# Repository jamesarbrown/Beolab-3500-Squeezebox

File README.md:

# Beolab-3500-Squeezebox

This project is to convert and Bang and Olufsen Beolab 3500 into a Logitech Media Server / Slimdevices Squeezebox using Raspberry Pi and PiCorePlayer.

My first Squeezebox1 I bought from the US direct, long long before it was into the UK and since the range has been obsoleted by Logitech I wanted something a bit more than a streamer alone. There is a lot of B&O stuff in our family and it was a natural way to go, and most elegant equipment that has like all electronic stuff is soon out of date.

The project has a requirement for 3d printed parts and homemade PCBs

In no way is this project affiliated or representative of Bang and Olufsen, Logitech or Slimdevices. I have utilised the logos in my fascia designs, but if they need removing as companies sometimes do, I can do that, but don't feel this harms your brand identities.

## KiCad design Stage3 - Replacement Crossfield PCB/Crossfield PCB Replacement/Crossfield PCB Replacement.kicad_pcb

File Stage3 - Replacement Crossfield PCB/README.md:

## Stage 3 - Replacement Crossfield and Ribbon Cables

### Ribbon Cable Replacements

| Function            | New Length    | Ways | Socket on Beolab   | RS PN Plugs   |
| ------------------- |:-------------:| :---:| :----------------: | ------------: |
| Right Hand Side Amp | 380mm         | 8    | P2                 | 680-5148      |
| Left Hand Side Amp  | 520mm         | 8    | P2                 | 680-5148      |
| Right Hand Side Amp | 370mm         | 12   | P18                | 680-4933      |
| TX "Left"           | 520mm         | 4    | P21                | 341-7349      |

Note 10 way ribbon P17 to P5 is removed and not replaced. On ribbon cable bought a length of 14 way and cut down for other sections

In later stages the right hand side and left hand amps will be swapped around to create space for the crossfield PCB

## Crossfield PCB Folders

I made the PCB utilising laser printer thermal transfer method. 

In the following folders please finds

### PDFs

Crossfield PCB.pdf - The PCB to Print

Crossfield Schematic.pdf - The Schematic of the above PCB

### Crossfield PCB Replacement (KiCAD Project)
The original KiCAD Design files, including the TE connectivity plugs and so on

#### Notes 
I had difficulty in nailing down the PFAIL and PLIM functions, so copied the way they originally were immplemented into the B&O microcomputer. Then used a BC549 to separate the circuit from the Raspberry. My suspicion was I could pull down the 3v3 directly, but went for this way to achieve some security.

### 3d from Kicad of PCB

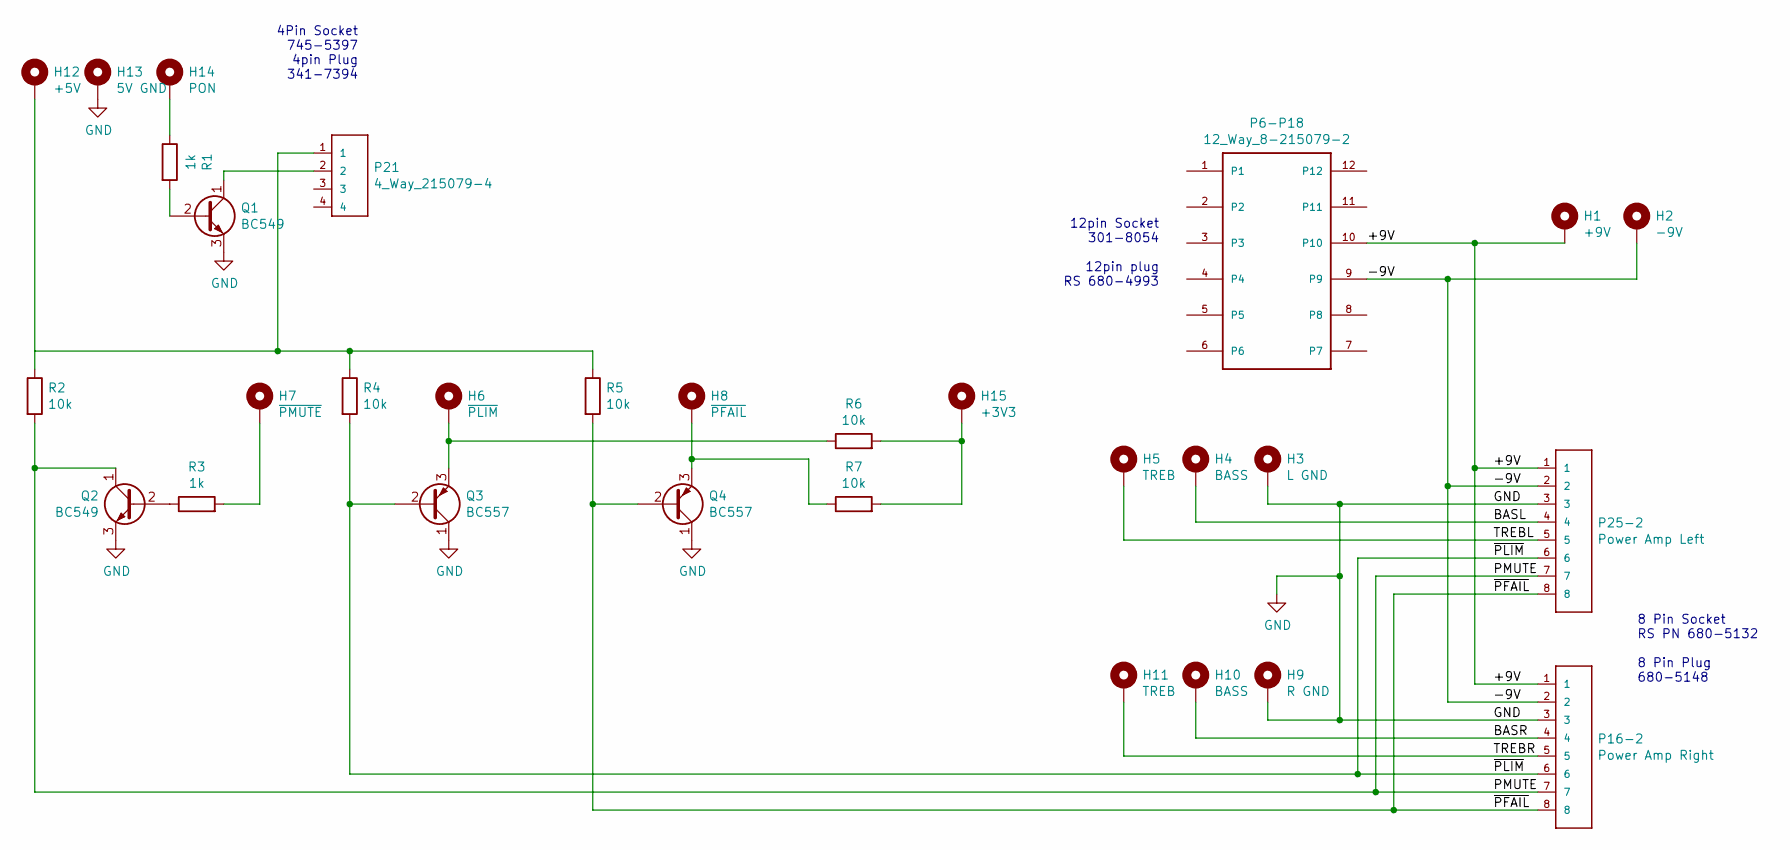
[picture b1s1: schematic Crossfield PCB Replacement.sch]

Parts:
H1: +9V; SolderWirePad_1x01_Drill1.2mm
H2: -9V; SolderWirePad_1x01_Drill1.2mm
H3: L GND; SolderWirePad_1x01_Drill1.2mm
H4, H10: BASS; SolderWirePad_1x01_Drill1.2mm
H5, H11: TREB; SolderWirePad_1x01_Drill1.2mm
H6: ~PLIM; SolderWirePad_1x01_Drill1.2mm
H7: ~PMUTE; SolderWirePad_1x01_Drill1.2mm
H8: ~PFAIL; SolderWirePad_1x01_Drill1.2mm
H9: R GND; SolderWirePad_1x01_Drill1.2mm
H12: +5V; SolderWirePad_1x01_Drill1.2mm
H13: 5V GND; SolderWirePad_1x01_Drill1.2mm
H14: PON; SolderWirePad_1x01_Drill1.2mm
H15: +3V3; SolderWirePad_1x01_Drill1.2mm
P6-P18: 12_Way_8-215079-2; TE_8-215079-2
P16-2: Power Amp Right; TE_215079-8
P21: 4_Way_215079-4; TE_215079-4
P25-2: Power Amp Left; TE_215079-8
Q1, Q2: BC549; TO-92_Inline
Q3, Q4: BC557; TO-92_Inline
R1, R3: 1k; R_Axial_DIN0204_L3.6mm_D1.6mm_P7.62mm_Horizontal
R2, R4, R5, R6, R7: 10k; R_Axial_DIN0204_L3.6mm_D1.6mm_P7.62mm_Horizontal

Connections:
/+9V: H1.1, P6-P18.10, P16-2.1, P25-2.1
/-9V: H2.1, P6-P18.9, P16-2.2, P25-2.2
/BASL: H4.1, P25-2.4
/BASR: H10.1, P16-2.4
/PMUTE: P16-2.7, P25-2.7, Q2.1 (C), R2.2
/TREBL: H5.1, P25-2.5
/TREBR: H11.1, P16-2.5
/~PFAIL: P16-2.8, P25-2.8, Q4.2 (B), R5.2
/~PLIM: P16-2.6, P25-2.6, Q3.2 (B), R4.2
GND: H3.1, H9.1, H13.1, P16-2.3, P25-2.3, Q1.3 (E), Q2.3 (E), Q3.1 (C), Q4.1 (C)
unnamed: H6.1, Q3.3 (E), R6.1
unnamed: H7.1, R3.2
unnamed: H8.1, Q4.3 (E), R7.1
unnamed: H12.1, P21.1, R2.1, R4.1, R5.1
unnamed: H14.1, R1.1
unnamed: H15.1, R6.2, R7.2
unnamed: P21.2, Q1.1 (C)
unnamed: Q1.2 (B), R1.2
unnamed: Q2.2 (B), R3.1

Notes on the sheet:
8 Pin Socket RS PN 680-5132 8 Pin Plug 680-5148
12pin Socket 301-8054 12pin plug RS 680-4993
4Pin Socket 745-5397 4pin Plug 341-7394

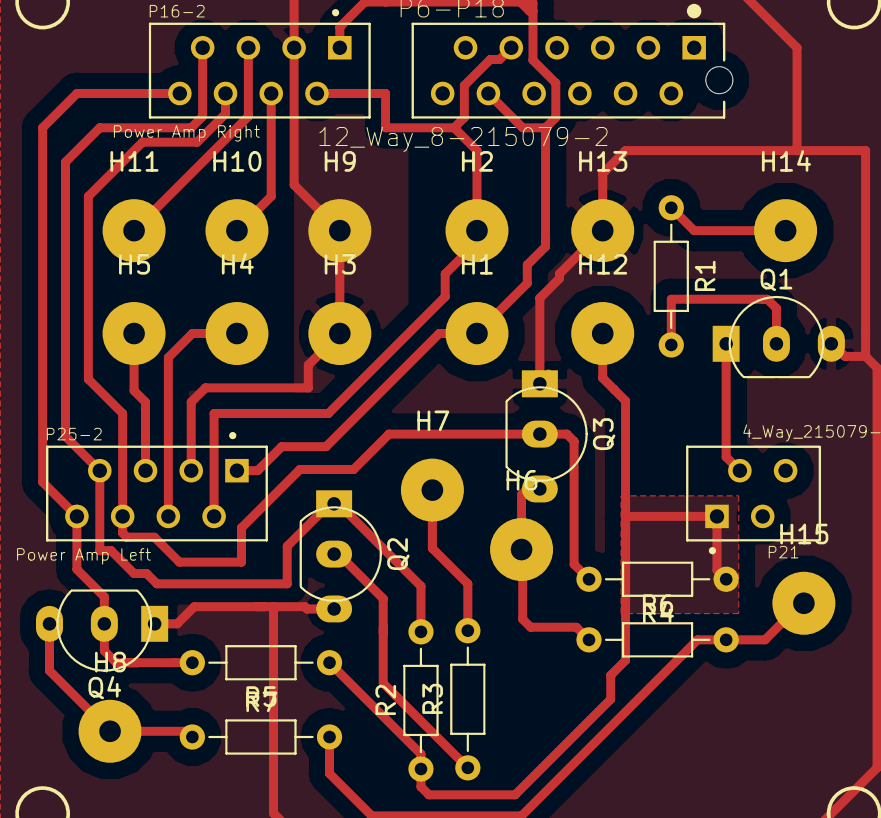
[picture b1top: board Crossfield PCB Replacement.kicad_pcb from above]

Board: 2 copper layers, 30 parts (0 on the bottom side), 19 nets.

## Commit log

2019-03-10 Added Support Info
2019-03-10 Added replacement speaker info
2019-03-10 Images new speaker
2019-03-10 Moved Image to image folder
2019-03-10 Rename of Image
2019-03-10 Added flashforge printer files
2019-03-10 Added Solidworks Part and Assy files
2019-03-10 Added Images of Fascia
2019-03-10 Added STL
2019-03-11 Added PCB and Schematic
2019-03-11 Added KiCAD FIles
2019-03-17 Fixed mains cable position holes
2019-03-17 Flashforge printer files
2019-03-17 First Stage of PSU Conversion
2019-03-17 Renamed Folders
2019-03-17 Added Flashforge printer files for speaker bracket
2019-03-17 Renamed Folder and rescalled image
2019-03-17 Modifications to Left TC assy
2019-03-17 Adjusted Cable holes to suit RS PN 817-8873
2019-03-17 Added Images in build Rear Casing
2019-03-17 New Printer Files for Rear Casing
2019-03-17 Fixed Pin No Ordering on 12 Way Connector
2019-03-18 Changed PCB now has USB PSU
    The B&O PSU failed to provide enough mA for the raspberry. Now the switchmode PSU has been removed and replaced with a standard USB brick.
2019-03-18 Amended the Ribbon Cables
    Removed the switchmode PSU at this stage
2019-03-18 Updated Crossfield Designs
    Removed the 14 way connector to the Switchmode PSU and added a 4 way connector direct to Left TX (operating the main power relay)
2019-03-18 Added 3dimage of Crossfield
2019-03-18 Added 3d Image
2019-03-18 Added rear plastics README
2019-03-19 Added images of USB power plug Stage
2019-03-23 Fixed Pinout on 12 pin connector
2019-03-23 Fixed PCB to suit new pin out
2019-03-23 PCB tweaks
2019-03-31 Updated PCB following tests on PMUTE
2019-03-31 Removed Duplicate PDFs
2019-03-31 Corrected PCB Image
2019-03-31 Widened legs on Transistors for easier working
2019-03-31 Fixed broken track
2019-04-06 Loaded correct schematic image
2019-04-06 Corrected to reflect the 3rd PSU attempt
2019-04-06 Added Overview Wiring
2019-04-06 Updated Readme to include wiring diagram
2019-04-06 Auto Power Script
2019-04-06 Changed $GPIO to $GPIO_POWER
2019-04-07 Updated software instructions and added control bash script
2019-04-07 Added some images
2019-04-07 Corrected Image Path
2019-04-07 Added zoomed image
2019-04-07 Changed image size and position
2020-11-12 Replacement Cover for Wall Bracket
2021-05-13 Added information about the KMTech Crossovers
